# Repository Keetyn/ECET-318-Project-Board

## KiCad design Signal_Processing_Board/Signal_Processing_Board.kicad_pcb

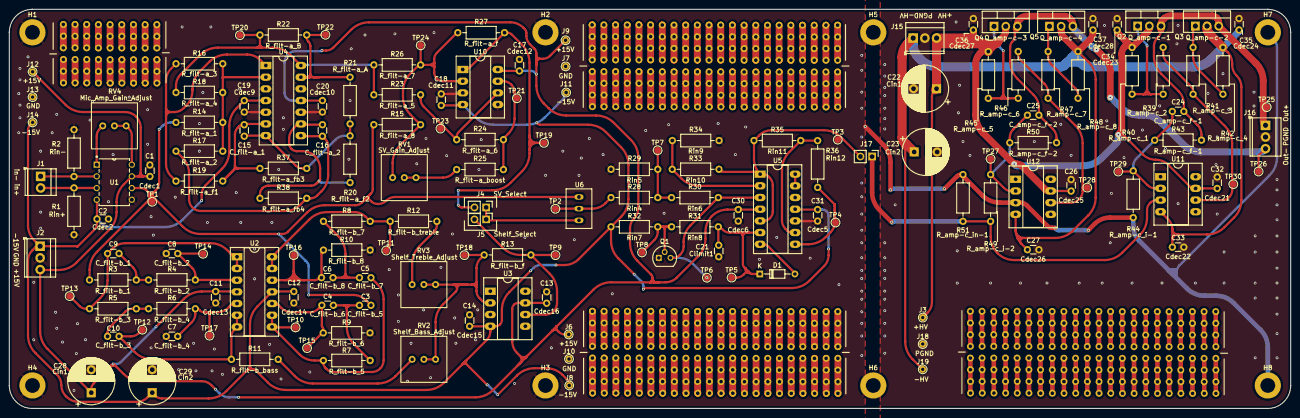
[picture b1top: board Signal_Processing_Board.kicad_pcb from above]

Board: 2 copper layers, 278.5 x 86.8 mm, 168 parts (0 on the bottom side), 63 nets.

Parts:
C1: Cdec1; C_Disc_D3.0mm_W1.6mm_P2.50mm
C2: Cdec2; C_Disc_D3.0mm_W1.6mm_P2.50mm
C3: C_filt-b_5; C_Disc_D3.0mm_W1.6mm_P2.50mm
C4: C_filt-b_6; C_Disc_D3.0mm_W1.6mm_P2.50mm
C5: C_filt-b_7; C_Disc_D3.0mm_W1.6mm_P2.50mm
C6: C_filt-b_8; C_Disc_D3.0mm_W1.6mm_P2.50mm
C7: C_filt-b_4; C_Disc_D3.0mm_W1.6mm_P2.50mm
C8: C_filt-b_2; C_Disc_D3.0mm_W1.6mm_P2.50mm
C9: C_filt-b_1; C_Disc_D3.0mm_W1.6mm_P2.50mm
C10: C_filt-b_3; C_Disc_D3.0mm_W1.6mm_P2.50mm
C11: Cdec13; C_Disc_D3.0mm_W1.6mm_P2.50mm
C12: Cdec14; C_Disc_D3.0mm_W1.6mm_P2.50mm
C13: Cdec16; C_Disc_D3.0mm_W1.6mm_P2.50mm
C14: Cdec15; C_Disc_D3.0mm_W1.6mm_P2.50mm
C15: C_filt-a_1; C_Disc_D3.0mm_W1.6mm_P2.50mm
C16: C_filt-a_2; C_Disc_D3.0mm_W1.6mm_P2.50mm
C17: Cdec12; C_Disc_D3.0mm_W1.6mm_P2.50mm
C18: Cdec11; C_Disc_D3.0mm_W1.6mm_P2.50mm
C19: Cdec9; C_Disc_D3.0mm_W1.6mm_P2.50mm
C20: Cdec10; C_Disc_D3.0mm_W1.6mm_P2.50mm
C21: Climit1; C_Disc_D3.0mm_W1.6mm_P2.50mm
C22, C28: Cin1; CP_Radial_D10.0mm_P5.00mm
C23, C29: Cin2; CP_Radial_D10.0mm_P5.00mm
C24: C_amp-c_f-1; C_Disc_D3.0mm_W1.6mm_P2.50mm
C25: C_amp-c_f-2; C_Disc_D3.0mm_W1.6mm_P2.50mm
C26: Cdec25; C_Disc_D3.0mm_W1.6mm_P2.50mm
C27: Cdec26; C_Disc_D3.0mm_W1.6mm_P2.50mm
C30: Cdec6; C_Disc_D3.0mm_W1.6mm_P2.50mm
C31: Cdec5; C_Disc_D3.0mm_W1.6mm_P2.50mm
C32: Cdec21; C_Disc_D3.0mm_W1.6mm_P2.50mm
C33: Cdec22; C_Disc_D3.0mm_W1.6mm_P2.50mm
C34: Cdec23; C_Disc_D3.0mm_W1.6mm_P2.50mm
C35: Cdec24; C_Disc_D3.0mm_W1.6mm_P2.50mm
C36: Cdec27; C_Disc_D3.0mm_W1.6mm_P2.50mm
C37: Cdec28; C_Disc_D3.0mm_W1.6mm_P2.50mm
D1: D; D_DO-34_SOD68_P7.62mm_Horizontal
H1, H2, H3, H4, H5, H6, H7, H8: MountingHole; MountingHole_3.2mm_M3_ISO7380_Pad
J1: Screw_Terminal_01x02; TerminalBlock_TE_282834-2_1x02_P2.54mm_Horizontal
J2, J15, J16: Screw_Terminal_01x03; TerminalBlock_TE_282834-3_1x03_P2.54mm_Horizontal
J3, J6, J7, J8, J9, J10, J11, J12, J13, J14, J18, J19: Conn_01x01_Socket; TestPoint_THTPad_D1.5mm_Drill0.7mm
J4, J5, J17: PinHeader_1x02_P2.54mm_Vertical
Q1: 2N3819; TO-92
Q2: Q_amp-c-1; TO-220-3_Vertical
Q3: Q_amp-c-2; TO-220-3_Vertical
Q4: Q_amp-c-3; TO-220-3_Vertical
Q5: Q_amp-c-4; TO-220-3_Vertical
R1: Rin+; R_Axial_DIN0207_L6.3mm_D2.5mm_P10.16mm_Horizontal
R2: Rin-; R_Axial_DIN0207_L6.3mm_D2.5mm_P10.16mm_Horizontal
R3: R_filt-b_1; R_Axial_DIN0207_L6.3mm_D2.5mm_P10.16mm_Horizontal
R4: R_filt-b_2; R_Axial_DIN0207_L6.3mm_D2.5mm_P10.16mm_Horizontal
R5: R_filt-b_3; R_Axial_DIN0207_L6.3mm_D2.5mm_P10.16mm_Horizontal
R6: R_filt-b_4; R_Axial_DIN0207_L6.3mm_D2.5mm_P10.16mm_Horizontal
R7: R_filt-b_5; R_Axial_DIN0207_L6.3mm_D2.5mm_P10.16mm_Horizontal
R8: R_filt-b_7; R_Axial_DIN0207_L6.3mm_D2.5mm_P10.16mm_Horizontal
R9: R_filt-b_6; R_Axial_DIN0207_L6.3mm_D2.5mm_P10.16mm_Horizontal
R10: R_filt-b_8; R_Axial_DIN0207_L6.3mm_D2.5mm_P10.16mm_Horizontal
R11: R_filt-b_bass; R_Axial_DIN0207_L6.3mm_D2.5mm_P10.16mm_Horizontal
R12: R_filt-b_treble; R_Axial_DIN0207_L6.3mm_D2.5mm_P10.16mm_Horizontal
R13: R_filt-b_f; R_Axial_DIN0207_L6.3mm_D2.5mm_P10.16mm_Horizontal
R14: R_filt-a_1; R_Axial_DIN0207_L6.3mm_D2.5mm_P10.16mm_Horizontal
R15: R_filt-a_8; R_Axial_DIN0207_L6.3mm_D2.5mm_P10.16mm_Horizontal
R16: R_filt-a_3; R_Axial_DIN0207_L6.3mm_D2.5mm_P10.16mm_Horizontal
R17: R_filt-a_2; R_Axial_DIN0207_L6.3mm_D2.5mm_P10.16mm_Horizontal
R18: R_filt-a_4; R_Axial_DIN0207_L6.3mm_D2.5mm_P10.16mm_Horizontal
R19: R_filt-a_f1; R_Axial_DIN0207_L6.3mm_D2.5mm_P10.16mm_Horizontal
R20: R_filt-a_f2; R_Axial_DIN0207_L6.3mm_D2.5mm_P10.16mm_Horizontal
R21: R_filt-a_A; R_Axial_DIN0207_L6.3mm_D2.5mm_P10.16mm_Horizontal
R22: R_filt-a_B; R_Axial_DIN0207_L6.3mm_D2.5mm_P10.16mm_Horizontal
R23: R_filt-a_5; R_Axial_DIN0207_L6.3mm_D2.5mm_P10.16mm_Horizontal
R24: R_filt-a_6; R_Axial_DIN0207_L6.3mm_D2.5mm_P10.16mm_Horizontal
R25: R_filt-a_boost; R_Axial_DIN0207_L6.3mm_D2.5mm_P10.16mm_Horizontal
R26: R_filt-a_7; R_Axial_DIN0207_L6.3mm_D2.5mm_P10.16mm_Horizontal
R27: R_filt-a_f; R_Axial_DIN0207_L6.3mm_D2.5mm_P10.16mm_Horizontal
R28: Rin4; R_Axial_DIN0207_L6.3mm_D2.5mm_P10.16mm_Horizontal
R29: Rin5; R_Axial_DIN0207_L6.3mm_D2.5mm_P10.16mm_Horizontal
R30: Rin6; R_Axial_DIN0207_L6.3mm_D2.5mm_P10.16mm_Horizontal
R31: Rin8; R_Axial_DIN0207_L6.3mm_D2.5mm_P10.16mm_Horizontal
R32: Rin7; R_Axial_DIN0207_L6.3mm_D2.5mm_P10.16mm_Horizontal
R33: Rin10; R_Axial_DIN0207_L6.3mm_D2.5mm_P10.16mm_Horizontal
R34: Rin9; R_Axial_DIN0207_L6.3mm_D2.5mm_P10.16mm_Horizontal
R35: Rin11; R_Axial_DIN0207_L6.3mm_D2.5mm_P10.16mm_Horizontal
R36: Rin12; R_Axial_DIN0207_L6.3mm_D2.5mm_P10.16mm_Horizontal
R37: R_filt-a_fb3; R_Axial_DIN0207_L6.3mm_D2.5mm_P10.16mm_Horizontal
R38: R_filt-a_fb4; R_Axial_DIN0207_L6.3mm_D2.5mm_P10.16mm_Horizontal
R39: R_amp-c_2; R_Axial_DIN0207_L6.3mm_D2.5mm_P10.16mm_Horizontal
R40: R_amp-c_1; R_Axial_DIN0207_L6.3mm_D2.5mm_P10.16mm_Horizontal
R41: R_amp-c_3; R_Axial_DIN0207_L6.3mm_D2.5mm_P10.16mm_Horizontal
R42: R_amp-c_4; R_Axial_DIN0207_L6.3mm_D2.5mm_P10.16mm_Horizontal
R43: R_amp-c_f-1; R_Axial_DIN0207_L6.3mm_D2.5mm_P10.16mm_Horizontal
R44: R_amp-c_i-1; R_Axial_DIN0207_L6.3mm_D2.5mm_P10.16mm_Horizontal
R45: R_amp-c_5; R_Axial_DIN0207_L6.3mm_D2.5mm_P10.16mm_Horizontal
R46: R_amp-c_6; R_Axial_DIN0207_L6.3mm_D2.5mm_P10.16mm_Horizontal
R47: R_amp-c_7; R_Axial_DIN0207_L6.3mm_D2.5mm_P10.16mm_Horizontal
R48: R_amp-c_8; R_Axial_DIN0207_L6.3mm_D2.5mm_P10.16mm_Horizontal
R49: R_amp-c_i-2; R_Axial_DIN0207_L6.3mm_D2.5mm_P10.16mm_Horizontal
R50: R_amp-c_f-2; R_Axial_DIN0207_L6.3mm_D2.5mm_P10.16mm_Horizontal
R51: R_amp-c_in-1; R_Axial_DIN0207_L6.3mm_D2.5mm_P10.16mm_Horizontal
RV1, RV2, RV3, RV4: R_Potentiometer; Trim Pot
TP1, TP2, TP3, TP4, TP5, TP6, TP7, TP8, TP9, TP10, TP11, TP12, TP13, TP14, TP15, TP16, TP17, TP18, TP19, TP20, TP21, TP22, TP23, TP24, TP25, TP26, TP27, TP28, TP29, TP30: TestPoint_Flag; TestPoint_Pad_D1.5mm
U1: INA128; P8
U2, U4, U5: TL084; CERDIP-14_W7.62mm_SideBrazed_LongPads_Socket
U3: TL081; CERDIP-8_W7.62mm_SideBrazed_LongPads_Socket
U6: 800CSP1B6M2QE
U7, U9, U13: BreadBoard Space XL
U8: BreadBoard Space
U10: TL082; CERDIP-8_W7.62mm_SideBrazed_LongPads_Socket
U11: U_amp-c_1; CERDIP-8_W7.62mm_SideBrazed_LongPads_Socket
U12: U_amp-c_2; CERDIP-8_W7.62mm_SideBrazed_LongPads_Socket

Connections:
+15V: C1.1, C11.2, C13.2, C17.2, C20.2, C28.1, C30.1, J2.3, J6.1, J9.1, J12.1, U1.7 (V+), U2.4 (V+), U3.7 (V+), U4.11 (V-), U5.4 (V+), U10.8 (V+)
+HV: C22.1, C26.1, C32.1, C34.1, C36.1, J3.1, J15.3, Q2.2 (D), Q4.2 (D), R40.1, R45.1, U11.7 (V+), U12.7 (V+)
-15V: C2.1, C12.1, C14.2, C18.2, C19.2, C29.1, C31.1, J2.1, J8.1, J11.1, J14.1, R32.1, U1.4 (V-), U2.11 (V-), U3.4 (V-), U4.4 (V+), U5.11 (V-), U10.4 (V-)
-HV: C23.1, C27.1, C33.1, C35.1, C37.1, J15.1, J19.1, Q3.2 (D), Q5.2 (D), R42.2, R48.2, U11.4 (V-), U12.4 (V-)
/Class_B_Discrete/Class_B_Discrete_Out_+: C24.2, J16.1, Q2.3 (S), Q3.3 (S), R43.2, TP25.1
/Class_B_Discrete/Class_B_Discrete_Out_-: C25.2, J16.3, Q4.3 (S), Q5.3 (S), R50.2, TP26.1
/Class_B_Discrete/Class_B_Discrete_in: J17.1, R49.2, R51.2, U11.3 (+)
/Mic Amp/Mic_Amp_Out: C3.1, R3.1, R14.1, R15.1, TP1.1, U1.6, U6.3
/Mic Amp/Mic_Amp_in+: J1.2, R1.1, U1.3 (+)
/Mic Amp/Mic_Amp_in-: J1.1, R2.1, U1.2 (-)
/Peak Limiter/Peak_Limit_Out+: J17.2, R33.2, R35.1, TP3.1, U5.1, U5.5 (+)
/Peak Limiter/Peak_Limit_Out-: R36.2, TP4.1, U5.8
/Peak Limiter/Peak_Limit_in: R28.1, TP2.1, U6.2
/Shelving Filter/Shelving_Filter_Out: J5.2, R13.2, TP9.1, U3.6 (Out)
/State Variable/State_Variable_Out: J4.2, R27.2, TP19.1, U10.1
GND: C1.2, C2.2, C7.1, C8.1, C11.1, C12.2, C13.1, C14.1, C17.1, C18.1, C19.1, C20.1, C21.2, C28.2, C29.2, C30.2, C31.2, H1.1, H2.1, H3.1, H4.1, H5.1, H6.1, H7.1, H8.1, J2.2, J7.1, J10.1, J13.1, Q1.1 (D), R1.2, R2.2, R9.1, R10.1, R29.1, R34.1, R44.1, R51.1, U1.5 (Ref), U3.3 (+), U4.3 (+), U4.5 (+), U4.10 (+), U4.12 (+), U5.10 (+), U5.12 (+), U10.3 (+), U10.5 (+), U12.3 (+)
GNDPWR: C22.2, C23.2, C26.2, C27.2, C32.2, C33.2, C34.2, C35.2, C36.2, C37.2, J15.2, J16.2, J18.1
unnamed: C3.2, C4.1, R7.1
unnamed: C5.2, C6.1, R8.1
unnamed: C9.2, R3.2, R4.1
unnamed: C10.2, R5.2, R6.1
unnamed: C15.2, R20.1, R21.2, R37.2, U4.7
unnamed: C16.2, R17.2, R38.2, U4.8
unnamed: D1.2 (A), U5.7
unnamed: C21.1, D1.1 (K), R31.2, TP5.1, U5.6 (-)
unnamed: J4.1, J5.1, U6.1
unnamed: Q1.2 (G), R31.1, R32.2, TP8.1
unnamed: Q1.3 (S), R30.2, TP6.1, U5.3 (+)
unnamed: Q2.1 (G), R39.1, R40.2
unnamed: Q3.1 (G), R41.2, R42.1
unnamed: Q4.1 (G), R45.2, R46.1
unnamed: Q5.1 (G), R47.2, R48.1
unnamed: R11.2, RV2.1
unnamed: R12.2, RV3.1
unnamed: R16.2, R19.1, U4.1
unnamed: R18.1, R22.1, R23.1, R26.1, TP20.1, U4.14
unnamed: R24.2, R25.1, TP21.1, U10.7
unnamed: R25.2, RV1.2, RV1.3
unnamed: R28.2, R29.2, R30.1, TP7.1
unnamed: RV4.1, U1.1 (Rg)
unnamed: RV4.2, RV4.3, U1.8 (Rg)
unnamed: C8.2, R4.2, TP14.1, U2.3 (+)
unnamed: C9.1, R5.1, TP13.1, U2.1, U2.2 (-)
unnamed: C7.2, R6.2, TP17.1, U2.5 (+)
unnamed: C10.1, R11.1, TP12.1, U2.6 (-), U2.7
unnamed: C4.2, R9.2, TP15.1, U2.10 (+)
unnamed: C5.1, R7.2, TP10.1, U2.8, U2.9 (-)
unnamed: C6.2, R10.2, TP16.1, U2.12 (+)
unnamed: R8.2, R12.1, TP11.1, U2.13 (-), U2.14
unnamed: R13.1, RV2.2, RV2.3, RV3.2, RV3.3, TP18.1, U3.2 (-)
unnamed: R14.2, R16.1, R17.1, R18.2, U4.2 (-)
unnamed: C15.1, R19.2, R37.1, U4.6 (-)
unnamed: C16.1, R20.2, R38.1, U4.9 (-)
unnamed: R21.1, R22.2, TP22.1, U4.13 (-)
unnamed: R33.1, R34.2, U5.2 (-)
unnamed: R35.2, R36.1, U5.9 (-)
unnamed: U5.13 (-), U5.14
unnamed: R15.2, R26.2, R27.1, RV1.1, TP24.1, U10.2 (-)
unnamed: R23.2, R24.1, TP23.1, U10.6 (-)
unnamed: C24.1, R43.1, R44.2, TP29.1, U11.2 (-)
unnamed: R39.2, R41.1, TP30.1, U11.6 (Out)
unnamed: C25.1, R49.1, R50.1, TP27.1, U12.2 (-)
unnamed: R46.2, R47.1, TP28.1, U12.6 (Out)

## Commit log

2024-08-30 First Revision, includes schematic & partial layout
2024-08-31 Mostly finished Layout and change U5 to TL084
2024-08-31 Including missed files
2024-09-01 Roughly finished component placeament and routing
2024-09-06 Added Breadboard Space and Test Points
2024-09-07 Updated file structure for multi-board design
2024-09-07 Roughly Finalized Signal processing board
2024-09-08 Created Power Board Project
2024-09-10 Minor updates to signal board, beginnings of power board
2024-09-10 Minor updates to the signal processing board
2024-09-13 Updated Schematic and initial layout of combined board
2024-09-14 First semi-finalized layout done
2024-09-14 Removed Power Board Directory
2024-09-14 Unfilled Zones for easier viewing
2024-09-15 First ordered version of Board
2024-09-15 Cleaned up some excess gerbers
2024-10-07 Final version of the board, updated with lessons from first version
2024-10-07 Updated file structure and added PDF of schematic
2024-10-07 Fixed missing PDF of schematic
2024-10-07 Making sure all changes are committed
